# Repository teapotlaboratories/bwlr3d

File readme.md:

# Teapot BWLR3D

Teapot BWLR3D is an Asset Tracker and Environmental Sensor with Solar Energy Harvesting. 
The device is capable of sensing temperature, humidity, air pressure, air quality, light intensity using the on-board **BME688** plus **VEM7700**, and calculate device's AHRS using the **LSM6DSOX** as accelerometer and gyrometer with **LIS3MDL** as magnetometer. 
Equiped with low-power **L86-M33** GNSS module, the device is capable to locate itself anywhere in the world.
With **STM32WLE** MCU as it's core and **AEM10941** for solar charging, the device is capable ultra-low power operation with the possibility of indefinite battery-life by utilizing the solar charging capability.

Teapot BWLR3D is part of  [Teapot open-hardware project](https://github.com/teapotlaboratories). 
  
## Disclaimer
- The 1KM range is based on [AERQ - Air Quality Monitoring](https://github.com/Mircerson/AERQ/) design, but have not been tested on this device yet
- The position of the **BME688** sensor on the board might not be the most efficient
- The position of the **LIS3MDL** sensor might get interference from the surrounding components and the provided magnetic case does interfere with the sensor.

## Future Works
- Develop code to read sensor and send data when movement is detected. **LSM6DSOX** can be set to ultra-low power mode and set to wake MCU when movement is detected, all other sensors needs to be in power-down mode.
- Change `SW4` wiring from GND to 3V3, to allow booting to STM32WLE USART Bootloader. This enable the user to flash the RAK3172 module using STM32CubeProgrammer without ST-Link.

## Specification

- [RAK3172](https://docs.rakwireless.com/Product-Categories/WisDuo/RAK3172-Module/Overview/): An STM32WLE5CC module
- [AEM10941](https://e-peas.com/product/aem10941): Solar energy harvesting chip
- On-board sensors:
	- [L86-M33](https://www.quectel.com/product/gnss-l86): GNSS module
	- [LSM6DSOX](https://www.st.com/en/mems-and-sensors/lsm6dsox.html): Accelerometer and Gyrometer
	- [LIS3MDL](https://www.st.com/en/mems-and-sensors/lis3mdl.html): Magnetometer
	- [VEML7700](https://www.vishay.com/docs/84286/veml7700.pdf): Ambient Light Intensity meter
	- [BME688](https://www.bosch-sensortec.com/products/environmental-sensors/gas-sensors/bme688): Environmental sensor
- 3.3V only power/pin. 
- 12uA Deep-Sleep
- Switchable TX Power. 14 dBm(50mA) or 22 dBm(140mA) ( on 915MHz frequency )
- Supports LoRaWAN 1.0.3
- 1KM+ Range
- UART2 breakout for **Arduino** progamming
- SWD breakout for **Mbed OS/STM32Cube** programming
- IPEX antenna connector 
- 3.7 Volts LiPo Battery

## Schematics

Schematic revisions:
-   Revision 1: Initial design
-   Revision 2: Swap BATT_MEAS and IMU_INT pin, and add 0.1uF to voltage divider 

## Boards
 <p align="center">  <br><b>PCB Render</b></p>

Built using KiCAD, the board is design to be as small as possible with all components placed on both side of the PCB.
The following design are based on the latest revision.
| Top Board | Bottom Board |
|--|--|
|  |  |
|  |  |

 <p align="center"> <br><b>PCB Top and Bottom Layout</b></p> 
  
### Case

Built using [TinkerCAD](https://www.tinkercad.com), the cases are available with 2 variant, with or without the programming port. The cases are 3D printable with any generic 3D printer with/without suppport (depends on the orientation). The STL files are available [here](https://github.com/teapotlaboratories/bwlr3d/tree/main/hardware/case)
 <p align="center"><br><b>Case Open</b></p>

The case is design to be as small as possible with an additional magnets in the back to ease the placement of the sensor. The following are the list of material used at the time of testing:
- 3.7v LiPo Battery, 500 mAh 50mm x 22mm x 48mm
- 4 piece of 8mm x 2mm neodymium magnet

<p align="center"><br><b>Sensor Placement with Magnet</b></p>

### Measurement
Power consumption and solar charging current are measured using [Nordic PPK2](https://www.nordicsemi.com/Products/Development-hardware/Power-Profiler-Kit-2)  and [CurrentRanger](https://lowpowerlab.com/shop/product/152).
The following are the summary of the measurement:
- Transmit 102 bytes @ 14dBm:  225ms @ 48mA
- Deep-Sleep : 12 uA
- GNSS Fix - Cold Start: 15s @ 38mA
- GNSS Fix - Hot Start: 5s @ 35mA
- Sensor Read: 1.36s @ 9mA
- Direct Sunlight Solar Charge: 12mA
- Indirect Sunlight Solar Charge: 454uA

Notes: 
- GNSS time to fix depends on the conditions of the sky

<p align="center"><br><b>LoRa Transmit</b></p>

<p align="center"><br><b>Deep-Sleep</b></p>

<p align="center"><br><b>GNSS Fix - Cold Start</b></p>

<p align="center"><br><b>GNSS Fix - Hot Start</b></p>

<p align="center"><br><b>Sensor Read</b></p>

| Solar Charge - Direct Sunlight | Solar Charge - Indirect Sunlight |
|--|--|
|  |  |

More measurement can be found [here](https://github.com/teapotlaboratories/bwlr3d/tree/main/docs/measurement)

### Bill Of Materials
Most of the components are generic and can be bought from any electornics/semi-conductor distributor. RAK3172 is the only component available in [RAKwireless store](https://store.rakwireless.com/products/wisduo-lpwan-module-rak3172?variant=40014759493830). The bill of materials can be downloaded [here](https://github.com/teapotlaboratories/bwlr3d/raw/main/hardware/bill_of_materials.csv)

> :warning: **Be sure to buy the RAK3172 variant without IPEX to use the On-Board Antenna** 

|Id |Designator                                           |Package                                |Quantity|Designation   |
|---|-----------------------------------------------------|---------------------------------------|--------|--------------|
|1  |BT1                                                  |JST_PH_S2B-PH-K_1x02_P2.00mm_Horizontal|1       |3.7v          |
|2  |C14,C23,C29                                          |C_0603_1608Metric                      |3       |1uF           |
|3  |C17,C31,C32,C1,C9,C22,C8,C10,C34,C13                 |C_0603_1608Metric                      |12      |10uF          |
|4  |C2,C4                                                |CP_EIA-3528-15_AVX-H_Pad1.50x2.35mm    |2       |330uF         |
|5  |C21                                                  |C_0603_1608Metric                      |1       |4.7uF         |
|6  |C27                                                  |C_0603_1608Metric                      |1       |2.2uF         |
|7  |C5,C20,C26,C12,C28,C19,C30,C11,C25,C3,C33,C24,C18,C35|C_0603_1608Metric                      |14      |0.1uF         |
|8  |C6                                                   |C_1210_3225Metric                      |1       |150uF         |
|9  |C7                                                   |C_0603_1608Metric                      |1       |22uF          |
|10 |D1                                                   |LED_0603_1608Metric                    |1       |RED           |
|11 |D2                                                   |LED_0603_1608Metric                    |1       |GREEN         |
|12 |E1                                                   |ANT-915-USP410                         |1       |ANT-915-USP410|
|13 |L2                                                   |IND_LPS4012-103MRB                     |1       |10uH          |
|14 |L3                                                   |L_0603_1608Metric                      |1       |10uH          |
|15 |Q1                                                   |SOT-23                                 |1       |PJA3407       |
|16 |Q2,Q4                                                |SOT-323_SC-70                          |2       |DMG1012UW     |
|17 |Q3                                                   |SOT-23                                 |1       |PMV27UPER     |
|18 |R1                                                   |R_0603_1608Metric                      |1       |4.7K          |
|19 |R11                                                  |R_0603_1608Metric                      |1       |100K          |
|20 |R12,R13,R5                                           |R_0603_1608Metric                      |3       |1K            |
|21 |R14                                                  |R_0603_1608Metric                      |1       |400K          |
|22 |R16                                                  |R_0603_1608Metric                      |6       |0             |
|23 |R7,R2,R3,R6,R21,R4                                   |R_0603_1608Metric                      |6       |10K           |
|24 |R9,R8,R19,R15,R18,R10,R17,R20                        |R_0603_1608Metric                      |8       |1M            |
|25 |SC4,SC1,SC3,SC2                                      |KXOB25-05X3F                           |4       |KXOB25-05X3F  |
|26 |SW3                                                  |SW_SPST_B3U-1000P                      |1       |RESET         |
|27 |SW4                                                  |SW_SPST_B3U-1000P                      |1       |BOOT          |
|28 |U1                                                   |BME688                                 |1       |BME688        |
|29 |U2                                                   |RAK3172                                |1       |RAK3172       |
|30 |U3                                                   |QFN-28-1EP_5x5mm_P0.5mm_EP3.35x3.35mm  |1       |AEM10941-QFN  |
|31 |U5                                                   |L86-M33                                |1       |L86-M33       |
|32 |U6,U4                                                |SOT-23-5                               |2       |XC6215        |
|33 |U7                                                   |PQFN50P250X300X97-14N_0.59x0.30        |1       |LSM6DSOXTR    |
|34 |U8                                                   |LGA12_ST                               |1       |LIS3MDL       |
|35 |U9                                                   |VEML7700-TT                            |1       |VEML7700-TT   |

## Programming

> :warning: **Board can only be powered using the LiPo Battery** 

Programming the device can be done over the **UART2** or **SWD**, available on the right side of the board.
Out of the factory, the RAK3172 chip ships with an **AT firmware** that can be tested by connecting a USB-to-UART bridge to the **UART2** port.

The following are some very good tutorial to start developing with the device:

 - [Communicating with the AT firmware](https://docs.rakwireless.com/Product-Categories/WisDuo/RAK3172-Module/Quickstart/#rak3172-as-a-lora-lorawan-modem-via-at-command)
 - [Programming with Arduino](https://docs.rakwireless.com/Product-Categories/WisDuo/RAK3172-Module/Quickstart/#rak3172-as-a-stand-alone-device-using-rui3)
 - [Programming with STM32Cube](https://docs.rakwireless.com/Product-Categories/WisDuo/RAK3172-Module/Low-Level-Development/#rak3172-on-stm32cubeide-with-stm32wl-sdk-v1-0-0)
 - [Programming with MbedOS](https://github.com/hallard/LoRa-E5-Tiny/blob/main/README.md#compile-and-flash-firmware)

For connecting to the **UART2** port, use any USB-to-UART bridge module. In testing, the [Sparkfun](https://www.sparkfun.com/products/14050) board is used for communication with AT firmware and programming over **Arduino**.
 <p align="center"> <br>Sparkfun USB-to-UART Bridge</p>

> :warning: **Be sure to only use 3.3V module. Do not 5V module** 

For connecting to the **SWD** port, use ST-Link v2  in-circuit debugger and programmer from STM. In testing, ST-Link v2 clone will not work. The ST-Link v2 should atleast be reconizeable by the [STM32CubeProgrammer](https://www.st.com/en/development-tools/stm32cubeprog.html).
A cheap and alternative way to get an authorized ST-Link is to buy a Nucleo board, cut the top part which contain the ST-Link and use it as an external programmer.
 <p align="center"> <br>ST-Link v2 from a Nucleo Development Board</p>
Here are some good tutorial to convert a Nucleo to and external ST-Link v2:

 - https://www.radioshuttle.de/en/turtle-en/nucleo-st-link-interface-en/
 - https://jeelabs.org/book/1547a/index.html

## Notes
There are some issue, notes, and behavior that was discovered at the time of testing and development. The following are those discovery:
- Soldering the solar cell is better to be done manually using a soldering iron. Without proper reflow oven, it may damage the solar cell and reduces it's efficiency
- PRIMIN is available to use as the input for AEM10941 Primary Battery input. See schematic for more detail	

## Reference
The project won't be possible without the amazing work from people across the globe. The following are the reference to those awesome projects:

 - [LoRa e5 Tiny](https://github.com/hallard/LoRa-E5-Tiny)
 - [AERQ - Air Quality Monitoring](https://github.com/Mircerson/AERQ/)
 - [TSEM](https://hackaday.io/project/159139-tiny-solar-energy-module-tsem)

## License
The product is open-source! However, some part of library used under **src**, might have it's own license.
Please reach out or create a ticket to report any license violation.

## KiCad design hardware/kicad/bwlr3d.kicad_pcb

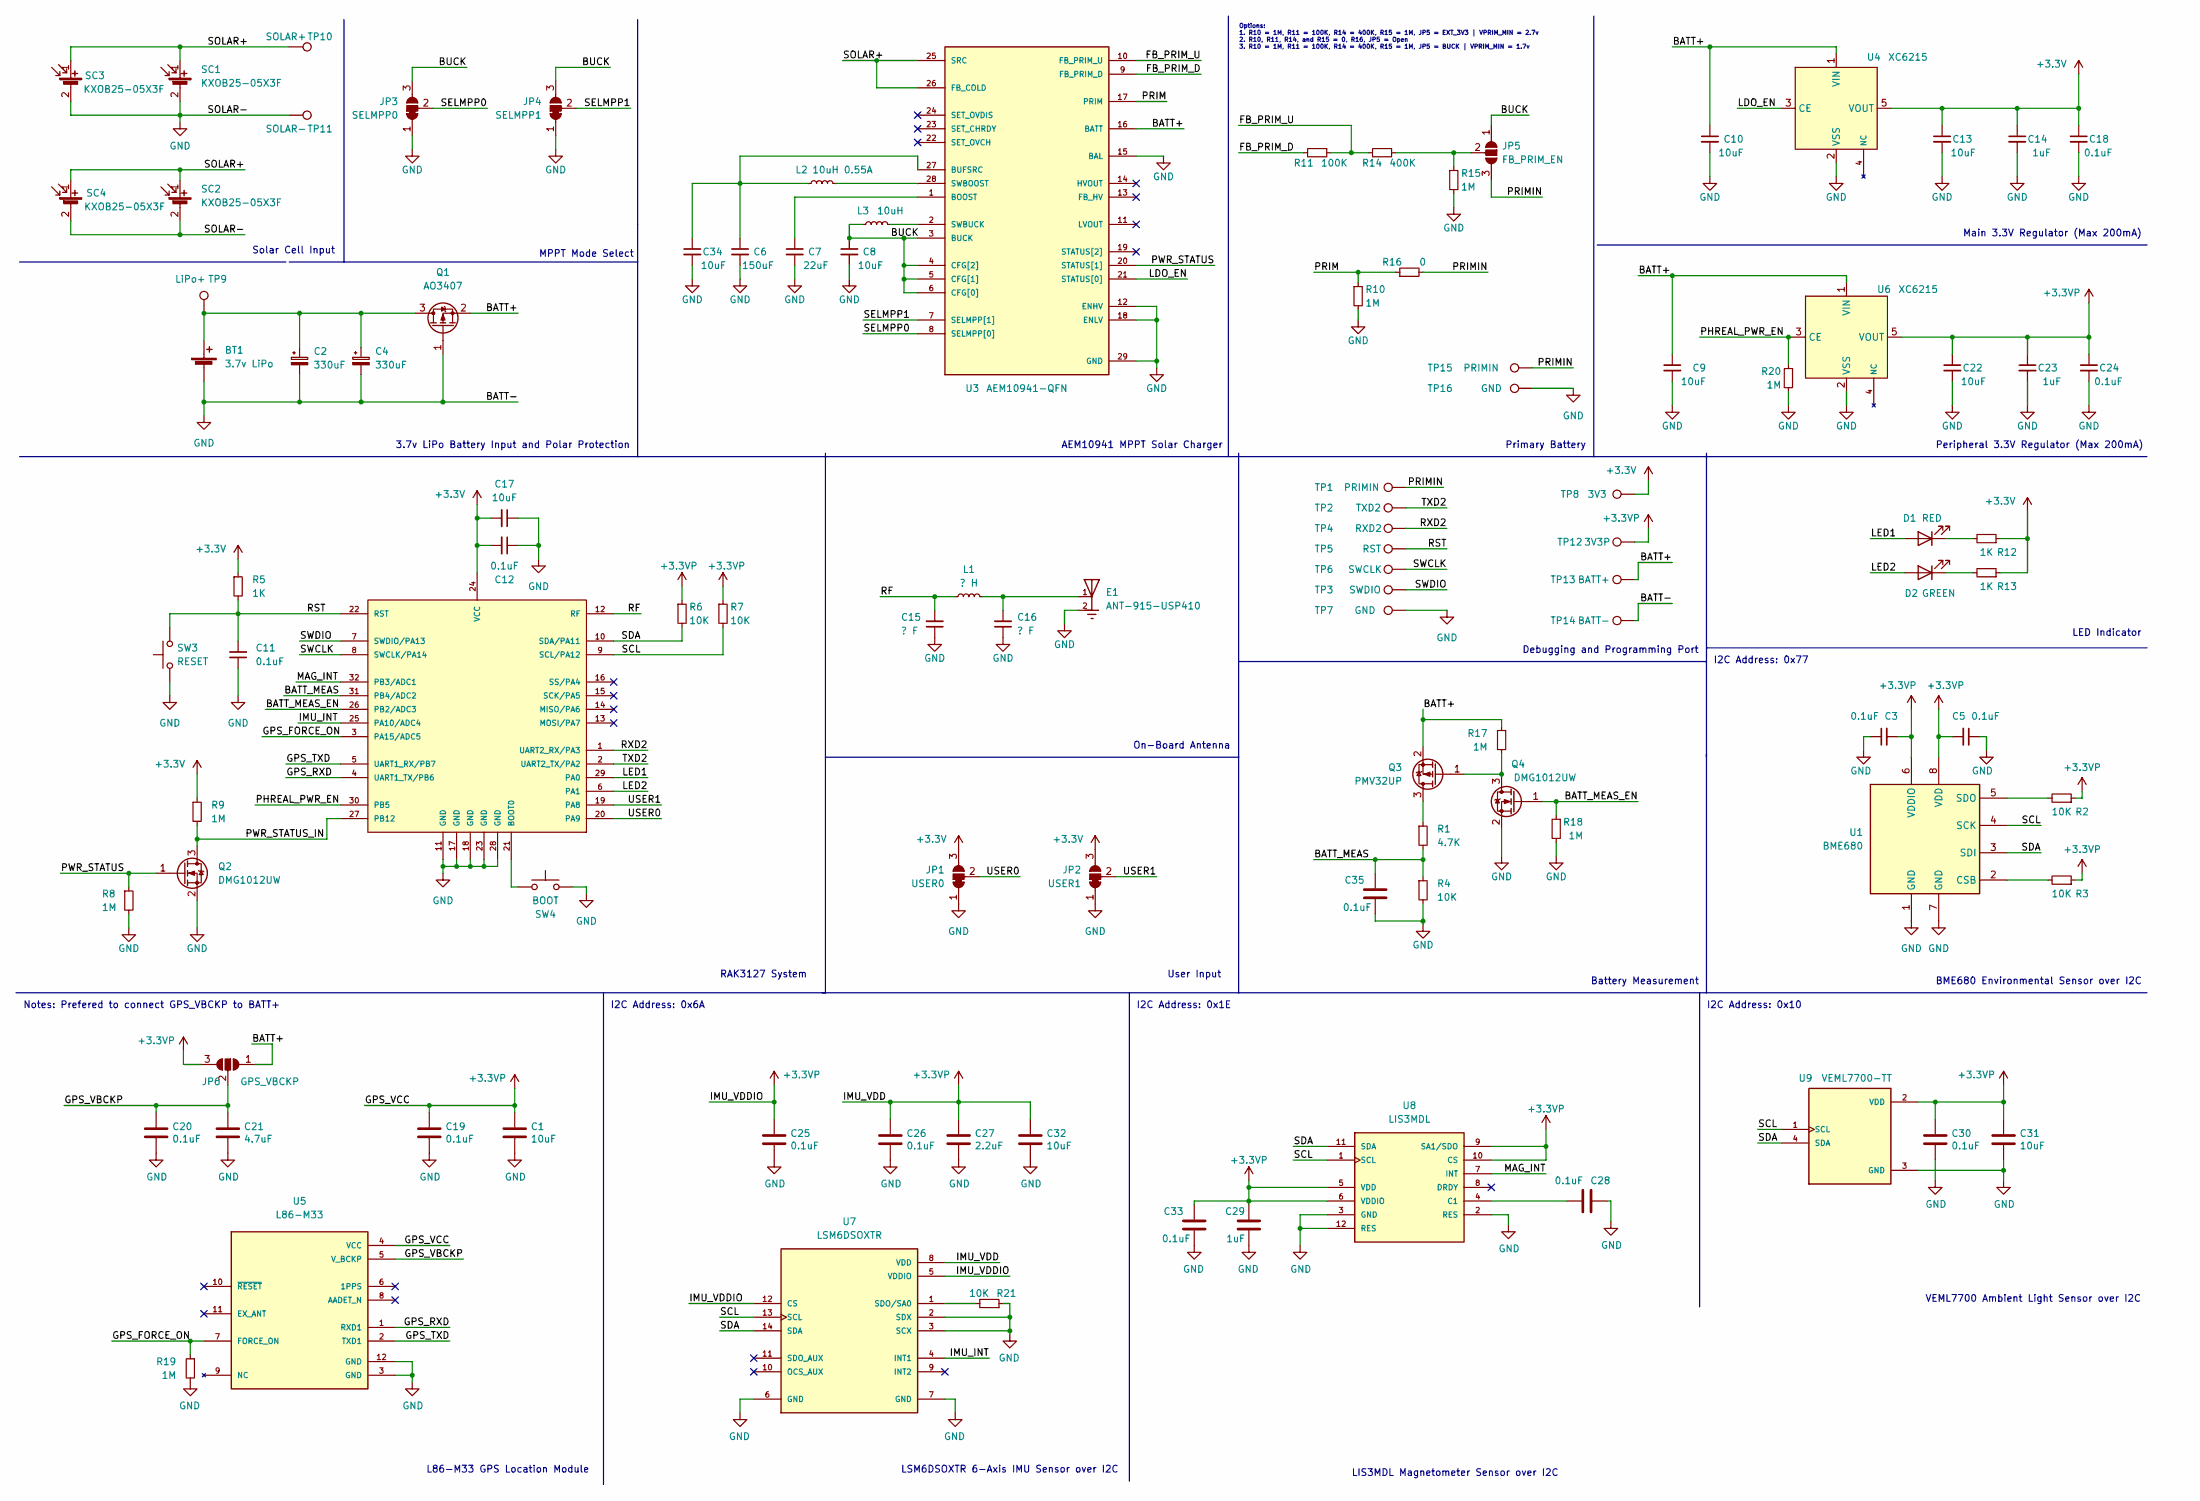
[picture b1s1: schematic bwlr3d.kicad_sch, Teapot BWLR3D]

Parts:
BT1: 3.7v LiPo; JST_PH_S2B-PH-K_1x02_P2.00mm_Horizontal
C1, C8, C9, C10, C13, C17, C22, C31, C32, C34: 10uF; C_0603_1608Metric
C2, C4: 330uF; CP_EIA-3528-15_AVX-H_Pad1.50x2.35mm_HandSolder
C3, C5, C11, C12, C18, C19, C20, C24, C25, C26, C28, C30, C33, C35: 0.1uF; C_0603_1608Metric
C6: 150uF; C_1210_3225Metric
C7: 22uF; C_0603_1608Metric
C14, C23, C29: 1uF; C_0603_1608Metric
C15, C16: ? F; C_0603_1608Metric
C21: 4.7uF; C_0603_1608Metric
C27: 2.2uF; C_0603_1608Metric
D1: RED; LED_0603_1608Metric
D2: GREEN; LED_0603_1608Metric
E1: ANT-915-USP410; XDCR_ANT-915-USP410; PARTREV N/A
JP1: USER0; SolderJumper-3_P1.3mm_Bridged12_RoundedPad1.0x1.5mm_NumberL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
JP2: USER1; SolderJumper-3_P1.3mm_Bridged12_RoundedPad1.0x1.5mm_NumberL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
JP3: SELMPP0; SolderJumper-3_P1.3mm_Bridged12_RoundedPad1.0x1.5mm_NumberL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
JP4: SELMPP1; SolderJumper-3_P1.3mm_Bridged12_RoundedPad1.0x1.5mm_NumberL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
JP5: FB_PRIM_EN; SolderJumper-3_P1.3mm_Open_RoundedPad1.0x1.5mm_NumberLabels
JP6: GPS_VBCKP; SolderJumper-3_P1.3mm_Open_RoundedPad1.0x1.5mm_NumberLabels
L1: ? H; L_0603_1608Metric
L2: 10uH 0.55A; IND_LPS4012-103MRB
L3: 10uH; L_0603_1608Metric
Q1: AO3407; SOT-23
Q2, Q4: DMG1012UW; SOT-323_SC-70
Q3: PMV32UP; SOT-23
R1: 4.7K; R_0603_1608Metric
R2, R3, R4, R6, R7, R21: 10K; R_0603_1608Metric
R5, R12, R13: 1K; R_0603_1608Metric
R8, R9, R10, R15, R17, R18, R19, R20: 1M; R_0603_1608Metric
R11: 100K; R_0603_1608Metric
R14: 400K; R_0603_1608Metric
R16: 0; R_0603_1608Metric
SC1, SC2, SC3, SC4: KXOB25-05X3F
SW3: RESET; SW_SPST_B3U-1000P
SW4: BOOT; SW_SPST_B3U-1000P
TP1: PRIMIN; TestPoint_Pad_1.5x1.5mm
TP2: TXD2; TestPoint_Pad_1.5x1.5mm
TP3: SWDIO; TestPoint_Pad_1.5x1.5mm
TP4: RXD2; TestPoint_Pad_1.5x1.5mm
TP5: RST; TestPoint_Pad_1.5x1.5mm
TP6: SWCLK; TestPoint_Pad_1.5x1.5mm
TP7: GND; TestPoint_Pad_1.5x1.5mm
TP8: 3V3; TestPoint_Pad_D1.0mm
TP9: LiPo+; TestPoint_Pad_D1.0mm
TP10: SOLAR+; TestPoint_Pad_D1.5mm
TP11: SOLAR-; TestPoint_Pad_D1.5mm
TP12: 3V3P; TestPoint_Pad_D1.0mm
TP13: BATT+; TestPoint_Pad_D1.0mm
TP14: BATT-; TestPoint_Pad_D1.0mm
TP15: PRIMIN; TestPoint_Pad_D2.0mm
TP16: GND; TestPoint_Pad_D2.0mm
U1: BME680; BME680-PSON80P300X300X100-8N
U2: RAK3172
U3: AEM10941-QFN; QFN-28-1EP_5x5mm_P0.5mm_EP3.35x3.35mm; PARTREV 1.4
U4, U6: XC6215; SOT-23-5_HandSoldering
U5: L86-M33; XCVR_L86-M33
U7: LSM6DSOXTR; PQFN50P250X300X97-14N_0.59x0.30
U8: LIS3MDL; LGA12_ST
U9: VEML7700-TT; XDCR_VEML7700-TT

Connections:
+3.3V: C12.2, C13.1, C14.1, C17.2, C18.1, JP1.3 (B), JP2.3 (B), R5.1, R9.1, R12.1, R13.1, TP8.1, U2.24 (VCC), U4.5 (VOUT)
+3.3VP: C1.1, C3.2, C5.2, C19.1, C22.1, C23.1, C24.1, C25.1, C26.1, C27.1, C29.1, C30.1, C31.1, C32.1, C33.2, JP6.3 (B), R2.1, R3.1, R6.1, R7.1, TP12.1, U1.6 (VDDIO), U1.8 (VDD), U5.4 (VCC), U6.5 (VOUT), U7.5 (VDDIO), U7.8 (VDD), U7.12 (CS), U8.5 (VDD), U8.6 (VDDIO), U8.9 (SA1/SDO), U8.10 (CS), U9.2 (VDD)
/BATT+: C9.1, C10.1, JP6.1 (A), Q1.2 (S), Q3.2 (S), R17.1, TP13.1, U3.16 (BATT), U4.1 (VIN), U6.1 (VIN)
/BATT_MEAS: C35.2, R1.2, R4.1, U2.31 (PB4/ADC2)
/BATT_MEAS_EN: Q4.1 (G), R18.1, U2.26 (PB2/ADC3)
/BUCK: C8.1, JP3.3 (B), JP4.3 (B), JP5.1 (A), L3.1, U3.3 (BUCK), U3.4 (CFG[2]), U3.5 (CFG[1]), U3.6 (CFG[0])
/FB_PRIM_D: R11.2, U3.9 (FB_PRIM_D)
/FB_PRIM_U: R11.1, R14.2, U3.10 (FB_PRIM_U)
/GPS_FORCE_ON: R19.1, U2.3 (PA15/ADC5), U5.7 (FORCE_ON)
/GPS_RXD: U2.4 (UART1_TX/PB6), U5.1 (RXD1)
/GPS_TXD: U2.5 (UART1_RX/PB7), U5.2 (TXD1)
/GPS_VBCKP: C20.1, C21.1, JP6.2 (C), U5.5 (V_BCKP)
/IMU_INT: U2.25 (PA10/ADC4), U7.4 (INT1)
/LDO_EN: U3.21 (STATUS[0]), U4.3 (CE)
/LED1: D1.2 (A), U2.29 (PA0)
/LED2: D2.2 (A), U2.6 (PA1)
/MAG_INT: U2.32 (PB3/ADC1), U8.7 (INT)
/PHREAL_PWR_EN: R20.1, U2.30 (PB5), U6.3 (CE)
/PRIM: R10.1, R16.1, U3.17 (PRIM)
/PRIMIN: JP5.3 (B), R16.2, TP1.1, TP15.1
/PWR_STATUS: Q2.1 (G), R8.1, U3.20 (STATUS[1])
/PWR_STATUS_IN: Q2.3 (D), R9.2, U2.27 (PB12)
/RF: C15.2, L1.1, U2.12 (RF)
/RST: C11.2, R5.2, SW3.2, TP5.1, U2.22 (RST)
/RXD2: TP4.1, U2.1 (UART2_RX/PA3)
/SCL: R7.2, U1.4 (SCK), U2.9 (SCL/PA12), U7.13 (SCL), U8.1 (SCL), U9.1 (SCL)
/SDA: R6.2, U1.3 (SDI), U2.10 (SDA/PA11), U7.14 (SDA), U8.11 (SDA), U9.4 (SDA)
/SELMPP0: JP3.2 (C), U3.8 (SELMPP[0])
/SELMPP1: JP4.2 (C), U3.7 (SELMPP[1])
/SOLAR+: SC1.1 (+), SC2.1 (+), SC3.1 (+), SC4.1 (+), TP10.1, U3.25 (SRC), U3.26 (FB_COLD)
/SWCLK: TP6.1, U2.8 (SWCLK/PA14)
/SWDIO: TP3.1, U2.7 (SWDIO/PA13)
/TXD2: TP2.1, U2.2 (UART2_TX/PA2)
/USER0: JP1.2 (C), U2.20 (PA9)
/USER1: JP2.2 (C), U2.19 (PA8)
GND: BT1.2 (-), C1.2, C2.2, C3.1, C4.2, C5.1, C6.2, C7.2, C8.2, C9.2, C10.2, C11.1, C12.1, C13.2, C14.2, C15.1, C16.1, C17.1, C18.2, C19.2, C20.2, C21.2, C22.2, C23.2, C24.2, C25.2, C26.2, C27.2, C28.2, C29.2, C30.2, C31.2, C32.2, C33.1, C34.2, C35.1, E1.2, JP1.1 (A), JP2.1 (A), JP3.1 (A), JP4.1 (A), Q1.1 (G), Q2.2 (S), Q4.2 (S), R4.2, R8.2, R10.2, R15.2, R18.2, R19.2, R20.2, R21.1, SC1.2 (-), SC2.2 (-), SC3.2 (-), SC4.2 (-), SW3.1, SW4.2, TP7.1, TP11.1, TP14.1, TP16.1, U1.1 (GND), U1.7 (GND), U2.11 (GND), U2.17 (GND), U2.18 (GND), U2.23 (GND), U2.28 (GND), U3.12 (ENHV), U3.15 (BAL), U3.18 (ENLV), U3.29 (GND), U4.2 (VSS), U5.3 (GND), U5.12 (GND), U6.2 (VSS), U7.2 (SDX), U7.3 (SCX), U7.6 (GND), U7.7 (GND), U8.2 (RES), U8.3 (GND), U8.12 (RES), U9.3 (GND)
unnamed: BT1.1 (+), C2.1, C4.1, Q1.3 (D), TP9.1
unnamed: C7.1, U3.1 (BOOST)
unnamed: C16.2, E1.1, L1.2
unnamed: C28.1, U8.4 (C1)
unnamed: C6.1, C34.1, L2.1, U3.27 (BUFSRC)
unnamed: D1.1 (K), R12.2
unnamed: D2.1 (K), R13.2
unnamed: JP5.2 (C), R14.1, R15.1
unnamed: L2.2, U3.28 (SWBOOST)
unnamed: L3.2, U3.2 (SWBUCK)
unnamed: Q3.1 (G), Q4.3 (D), R17.2
unnamed: Q3.3 (D), R1.1
unnamed: R2.2, U1.5 (SDO)
unnamed: R3.2, U1.2 (CSB)
unnamed: R21.2, U7.1 (SDO/SA0)
unnamed: SW4.1, U2.21 (BOOT0)

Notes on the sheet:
On-Board Antenna
RAK3127 System
I2C Address: 0x1E
MPPT Mode Select
BME680 Environmental Sensor over I2C
LED Indicator
LSM6DSOXTR 6-Axis IMU Sensor over I2C
AEM10941 MPPT Solar Charger
Notes: Prefered to connect GPS_VBCKP to BATT+
Battery Measurement
LIS3MDL Magnetometer Sensor over I2C
VEML7700 Ambient Light Sensor over I2C
I2C Address: 0x6A
Solar Cell Input
L86-M33 GPS Location Module
I2C Address: 0x10
Primary Battery
3.7v LiPo Battery Input and Polar Protection
User Input
I2C Address: 0x77
Peripheral 3.3V Regulator (Max 200mA)
Main 3.3V Regulator (Max 200mA)
Options: 1. R10 = 1M, R11 = 100K, R14 = 400K, R15 = 1M, JP5 = EXT_3V3 | VPRIM_MIN = 2.7v 2. R10, R11, R14, and R15 = 0, R16, JP5 = Open 3. R10 = 1M, R11 = 100K, R14 = 400K, R15 = 1M, JP5 = BUCK | VPRIM_MIN = 1.7v
Debugging and Programming Port

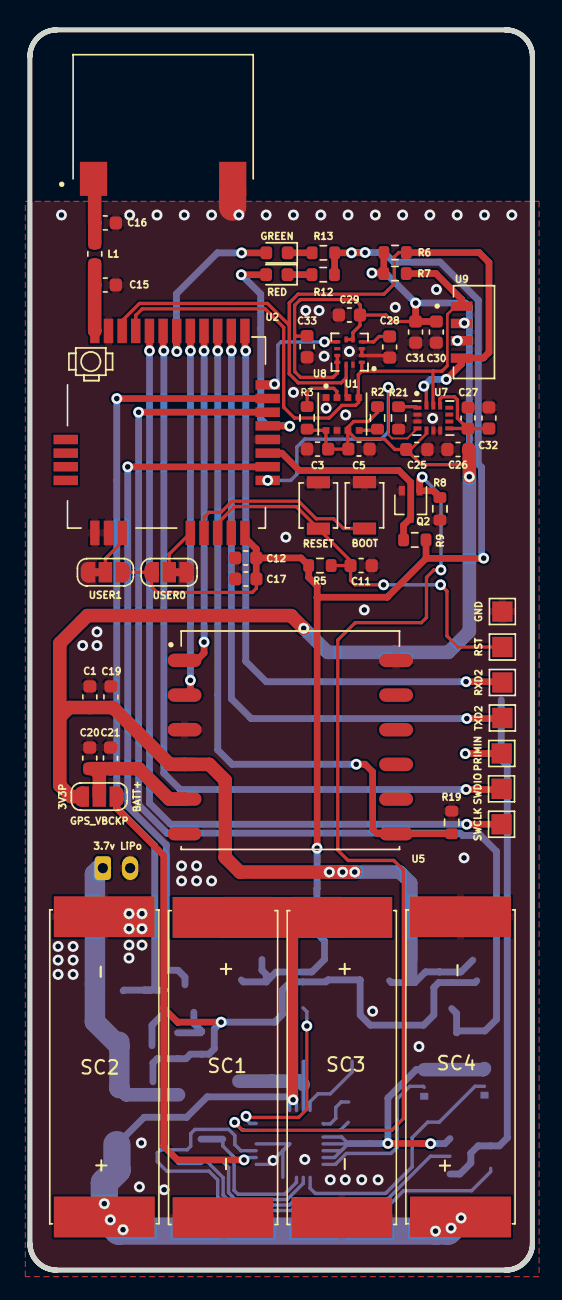
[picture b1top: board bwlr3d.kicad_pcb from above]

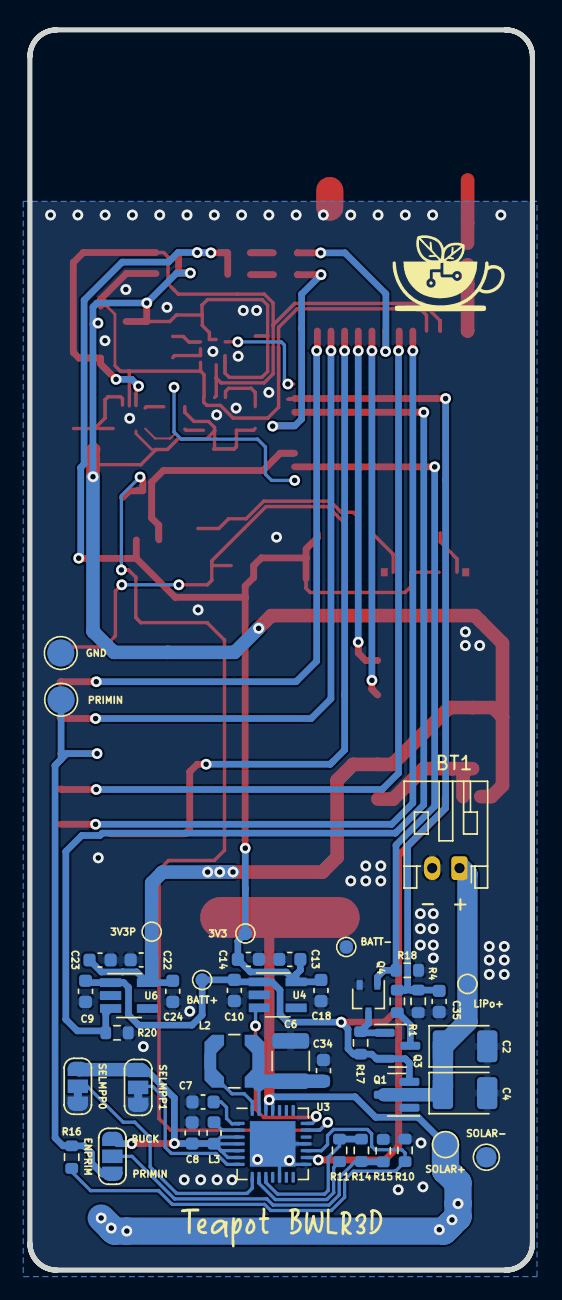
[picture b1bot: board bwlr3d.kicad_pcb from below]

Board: 2 copper layers, 36.8 x 90.9 mm, 104 parts (46 on the bottom side), 52 nets.

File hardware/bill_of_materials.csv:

Id,Designator,Package,Quantity,Designation
1,BT1,JST_PH_S2B-PH-K_1x02_P2.00mm_Horizontal,1,3.7v
2,"C14,C23,C29",C_0603_1608Metric,3,1uF
3,"C17,C31,C32,C1,C9,C22,C8,C10,C34,C13",C_0603_1608Metric,12,10uF
4,"C2,C4",CP_EIA-3528-15_AVX-H_Pad1.50x2.35mm,2,330uF
5,C21,C_0603_1608Metric,1,4.7uF
6,C27,C_0603_1608Metric,1,2.2uF
7,"C5,C20,C26,C12,C28,C19,C30,C11,C25,C3,C33,C24,C18,C35",C_0603_1608Metric,14,0.1uF
8,C6,C_1210_3225Metric,1,150uF
9,C7,C_0603_1608Metric,1,22uF
10,D1,LED_0603_1608Metric,1,RED
11,D2,LED_0603_1608Metric,1,GREEN
12,E1,ANT-915-USP410,1,ANT-915-USP410
13,L2,IND_LPS4012-103MRB,1,10uH
14,L3,L_0603_1608Metric,1,10uH
15,Q1,SOT-23,1,PJA3407
16,"Q2,Q4",SOT-323_SC-70,2,DMG1012UW
17,Q3,SOT-23,1,PMV27UPER
18,R1,R_0603_1608Metric,1,4.7K
19,R11,R_0603_1608Metric,1,100K
20,"R12,R13,R5",R_0603_1608Metric,3,1K
21,R14,R_0603_1608Metric,1,400K
22,R16,R_0603_1608Metric,6,0
23,"R7,R2,R3,R6,R21,R4",R_0603_1608Metric,6,10K
24,"R9,R8,R19,R15,R18,R10,R17,R20",R_0603_1608Metric,8,1M
25,"SC4,SC1,SC3,SC2",KXOB25-05X3F,4,KXOB25-05X3F
26,SW3,SW_SPST_B3U-1000P,1,RESET
27,SW4,SW_SPST_B3U-1000P,1,BOOT
28,U1,BME688,1,BME688
29,U2,RAK3172,1,RAK3172
30,U3,QFN-28-1EP_5x5mm_P0.5mm_EP3.35x3.35mm,1,AEM10941-QFN
31,U5,L86-M33,1,L86-M33
32,"U6,U4",SOT-23-5,2,XC6215
33,U7,PQFN50P250X300X97-14N_0.59x0.30,1,LSM6DSOXTR
34,U8,LGA12_ST,1,LIS3MDL
35,U9,VEML7700-TT,1,VEML7700-TT

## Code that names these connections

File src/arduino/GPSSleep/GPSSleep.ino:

#include <TinyGPSPlus.h>

// Teapot BWLR3D pins
#define LED0                PA0
#define LED1                PA1
#define PERIPHERAL_POWER_EN PB5
#define BATT_MEASURE_EN     PB2
#define POWER_STATUS        PB12
#define GPS_FORCE_ON        PA15
#define GPS_TXD             PB7
#define GPS_RXD             PB6
#define I2C_SDA             PA11
#define I2C_SCL             PA12
#define MAG_INT             PB3
#define IMU_INT             PA10   // new rev is PA10
#define BATT_MEASURE        PB4  // new rev is PB4

// The TinyGPSPlus object
TinyGPSPlus gps;

void setup()
{
  // initialize pins
  initializeSystem();
  
  // power-on all peripheral
  powerPeripheral(true);

  enableGPS();
  
  Serial.println();
  Serial.println(F("Sats HDOP  Latitude   Longitude   Fix  Date       Time     Date Alt    Chars Sentences Checksum"));
  Serial.println(F("           (deg)      (deg)       Age                      Age  (m)    RX    RX        Fail"));
  Serial.println(F("------------------------------------------------------------------------------------------------"));
}


uint32_t start_time;
uint32_t stop_at_time = 600000; // disable GPS every 10 minute
uint32_t sleep_time = 5000; // sleep for 5 seconds
void loop()
{
  /* print incoming GPS data */
  printInt(gps.satellites.value(), gps.satellites.isValid(), 5);
  printFloat(gps.hdop.hdop(), gps.hdop.isValid(), 6, 1);
  printFloat(gps.location.lat(), gps.location.isValid(), 11, 6);
  printFloat(gps.location.lng(), gps.location.isValid(), 12, 6);
  printInt(gps.location.age(), gps.location.isValid(), 5);
  printDateTime(gps.date, gps.time);
  printFloat(gps.altitude.meters(), gps.altitude.isValid(), 7, 2);
  printInt(gps.charsProcessed(), true, 6);
  printInt(gps.sentencesWithFix(), true, 10);
  printInt(gps.failedChecksum(), true, 9);
  Serial.println();
  
  smartDelay(1000);

  if (millis() > 5000 && gps.charsProcessed() < 10)
    Serial.println(F("No GPS data received: check wiring"));


  /* set gps to sleep every stop_at_time ms */
  if( start_time == 0 ){
    start_time = millis();
  }
  if( millis() - start_time > stop_at_time ){

    // disable gps
    disableGPS();
    
    // power-off all peripheral
    powerPeripheral(  false );

    // set device to sleep
    Serial.println("Set device to sleep");
    api.system.sleep.all(sleep_time);

    // wake gps
    enableGPS();
    
    // poweron all peripheral
    powerPeripheral(  true );


    // reset timer
    start_time = millis();
  }
}

static void setGPSToBackupMode()
{
  // prepare command
  unsigned char backup_mode_command[15];
  String base_backup_mode_command = ("$PMTK225,4*2F"); 
  const char tr[] = {0xD, 0xA};
  base_backup_mode_command.getBytes(backup_mode_command, sizeof(backup_mode_command));
  memcpy(backup_mode_command+13, tr, 2); 

  // for debug, print actual backup mode command
  Serial.print("Backup Mode Command: ");
  for( int i = 0; i < sizeof(backup_mode_command); i++ ) {  
    Serial.print("0x");
    Serial.print(backup_mode_command[i],HEX);
    Serial.print(" ");
  }
  Serial.println();
  
  Serial.println("Set GPS to Backup mode");
  Serial1.write(backup_mode_command, sizeof(backup_mode_command));
}

// This custom version of delay() ensures that the gps object
// is being "fed".
static void smartDelay(unsigned long ms)
{
  unsigned long start = millis();
  do 
  {
    while (Serial1.available())
      gps.encode(Serial1.read());
  } while (millis() - start < ms);
}

static void printFloat(float val, bool valid, int len, int prec)
{
  if (!valid)
  {
    while (len-- > 1)
      Serial.print('*');
    Serial.print(' ');
  }
  else
  {
    Serial.print(val, prec);
    int vi = abs((int)val);
    int flen = prec + (val < 0.0 ? 2 : 1); // . and -
    flen += vi >= 1000 ? 4 : vi >= 100 ? 3 : vi >= 10 ? 2 : 1;
    for (int i=flen; i<len; ++i)
      Serial.print(' ');
  }
  smartDelay(0);
}

static void printInt(unsigned long val, bool valid, int len)
{
  char sz[32] = "*****************";
  if (valid)
    sprintf(sz, "%ld", val);
  sz[len] = 0;
  for (int i=strlen(sz); i<len; ++i)
    sz[i] = ' ';
  if (len > 0) 
    sz[len-1] = ' ';
  Serial.print(sz);
  smartDelay(0);
}

static void printDateTime(TinyGPSDate &d, TinyGPSTime &t)
{
  if (!d.isValid())
  {
    Serial.print(F("********** "));
  }
  else
  {
    char sz[32];
    sprintf(sz, "%02d/%02d/%02d ", d.month(), d.day(), d.year());
    Serial.print(sz);
  }
  
  if (!t.isValid())
  {
    Serial.print(F("******** "));
  }
  else
  {
    char sz[32];
    sprintf(sz, "%02d:%02d:%02d ", t.hour(), t.minute(), t.second());
    Serial.print(sz);
  }

  printInt(d.age(), d.isValid(), 5);
  smartDelay(0);
}

static void printStr(const char *str, int len)
{
  int slen = strlen(str);
  for (int i=0; i<len; ++i)
    Serial.print(i<slen ? str[i] : ' ');
  smartDelay(0);
}

void powerPeripheral(bool power){
  if( power ){
    
    enableSensorCommunication();
    pinMode(PERIPHERAL_POWER_EN, OUTPUT);
    digitalWrite(PERIPHERAL_POWER_EN, HIGH);
  } else {
    
    disableSensorCommunication();    
    pinMode(PERIPHERAL_POWER_EN, OUTPUT);
    digitalWrite(PERIPHERAL_POWER_EN, LOW);
    delay( 1000 );
    pinMode(PERIPHERAL_POWER_EN, INPUT);  
  }
  delay( 1000 );
}

void initializeSystem(){  
  api.system.restoreDefault();
  Serial.begin(115200);

  // initialize power pin
  pinMode(PERIPHERAL_POWER_EN, INPUT);
    
  // disable unnecessary pin
  pinMode(MAG_INT, INPUT);
  pinMode(IMU_INT, INPUT);
  pinMode(POWER_STATUS, INPUT);
  pinMode(BATT_MEASURE, INPUT);
  pinMode(BATT_MEASURE_EN, INPUT);
  pinMode(LED0, OUTPUT);
  digitalWrite(LED0, HIGH);
  pinMode(LED1, OUTPUT);
  digitalWrite(LED1, HIGH);
  pinMode(GPS_FORCE_ON, INPUT); // open pin to allow GPS to go to sleep (backup mode)
}

void enableSensorCommunication() {
  // enable GPS serial
  Serial1.begin(9600);
  
  // enable sensor I2C bus
  Wire.begin();
}

void disableSensorCommunication() {
  // disable GPS serial
  Serial1.end();
  pinMode(GPS_TXD, INPUT);
  pinMode(GPS_RXD, INPUT);

  // disable I2C
  Wire.end();
  pinMode(I2C_SDA, INPUT);
  pinMode(I2C_SCL, INPUT);
}

void enableGPS(){
  // wake gps, incase it's off
  pinMode(GPS_FORCE_ON, OUTPUT);
  digitalWrite(GPS_FORCE_ON, HIGH);
}

void disableGPS(){  
    // open pin to allow GPS to go to sleep (backup mode)
    pinMode(GPS_FORCE_ON, INPUT);
    // Set GPS to Backup mode
    setGPSToBackupMode();
    delay(1000);
}

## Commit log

2022-08-25 add teapot kicad library
2022-09-03 update library
2022-09-03 update library and footprint
2022-09-25 switch IMU_INT with BATT_MEAS, switch I2C pull-up to 3V3P, and add GND stitch
2022-09-25 add code example
2022-10-02 update test code
2022-10-08 updated example code
2022-10-09 add working AHRS
2022-10-09 update IMUTest
2022-10-11 update ahrs test
2022-11-09 change voltage divider value to 4.7K and 10K, add 0.1uF capacitor to voltage divider
2022-11-09 release board revision 1
2022-11-09 add remaining hardware files
2022-11-09 update src code example
2022-11-09 update source code example
2022-11-11 update source code
2022-11-13 initial working code
2022-11-14 add support for uplink process confirmation
2022-11-14 update src
2022-11-14 power-off gnss module when not needed
2022-11-17 add images for docs
2022-11-17 add measurement docs
2022-11-17 add deep sleep measurement
2022-11-17 change revision number
2022-11-17 add src/arduino readme
2022-11-18 initial readme
2022-11-18 add 3d assembedled board
2022-11-18 add measurement readme
2022-11-19 release teapot bwlr3d rev 2
2022-11-19 update src/arduino readme
2022-11-20 change crc16 to crc16-ccitt
2022-11-22 add tools to parse encoded SimpleLoRaApplication payload
2022-11-24 add tools to log wisgate report to csv
2024-08-06 update bill of materials and name file

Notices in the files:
readme.md:
License:
License: MIT
